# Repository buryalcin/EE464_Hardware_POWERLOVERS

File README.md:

# EE464_Hardware_POWERLOVERS
EE464 Hardware Project Repo by Burak Yalçın &amp; Emre Deniz Şenel

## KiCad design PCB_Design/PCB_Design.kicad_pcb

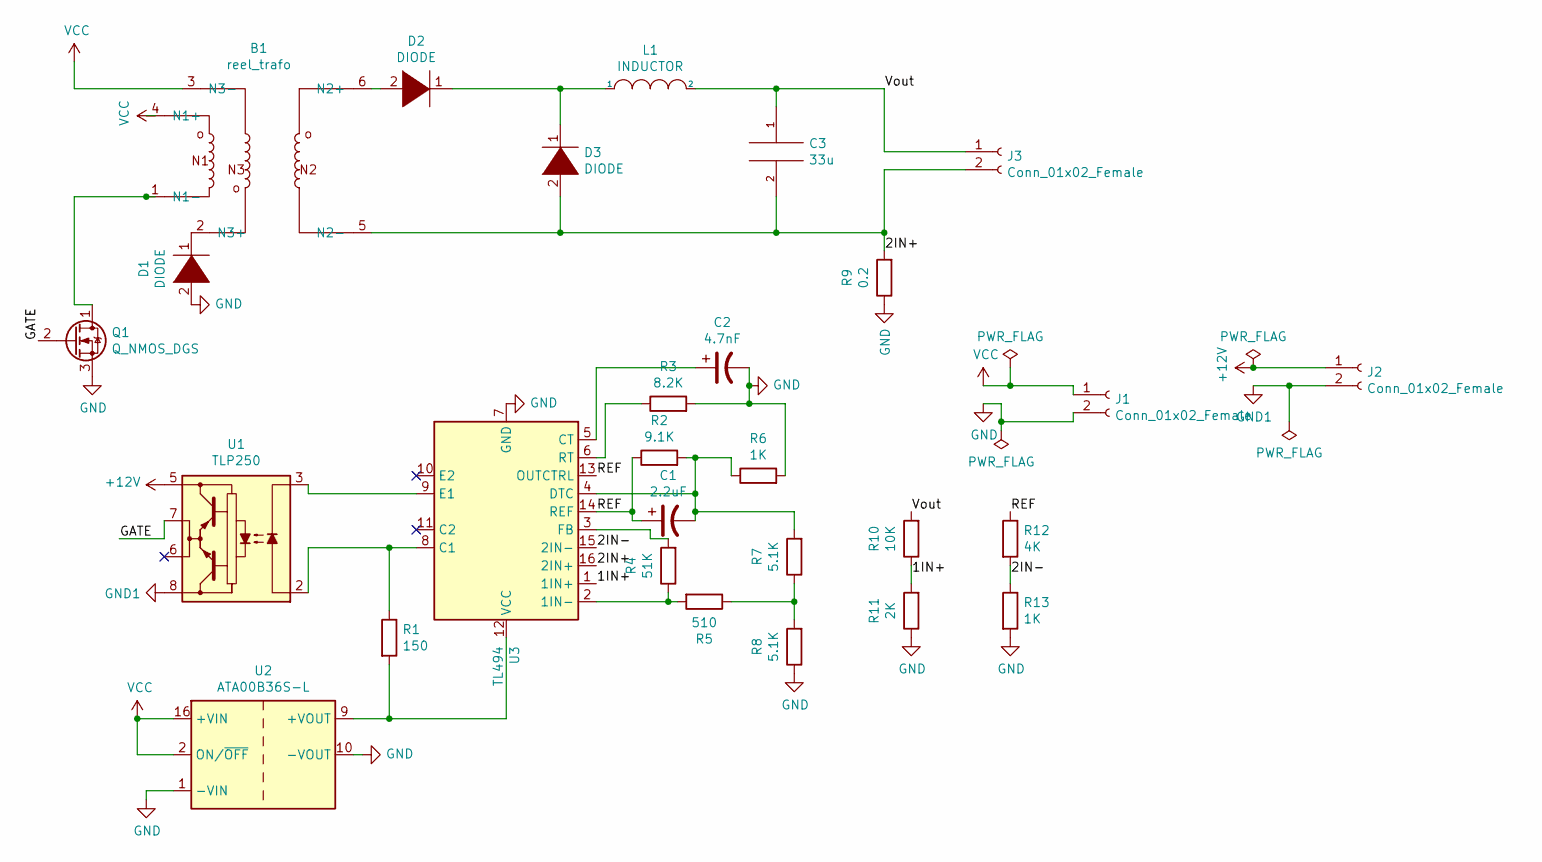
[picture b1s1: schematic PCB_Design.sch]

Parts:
B1: reel_trafo; trafo
C1: 2.2uF; C_1206_3216Metric_Pad1.42x1.75mm_HandSolder
C2: 4.7nF; C_1206_3216Metric_Pad1.42x1.75mm_HandSolder
C3: 33u; C_1206_3216Metric_Pad1.42x1.75mm_HandSolder
D1, D2, D3: DIODE; TO-277A
J1, J2, J3: Conn_01x02_Female; Banana_Jack_2Pin
L1: INDUCTOR; L_Toroid_Horizontal_D32.5mm_P28.90mm_Bourns_2300
Q1: Q_NMOS_DGS; PQFN_8x8
R1: 150; R_Axial_DIN0309_L9.0mm_D3.2mm_P12.70mm_Horizontal
R2: 9.1K; R_Axial_DIN0309_L9.0mm_D3.2mm_P12.70mm_Horizontal
R3: 8.2K; R_Axial_DIN0309_L9.0mm_D3.2mm_P12.70mm_Horizontal
R4: 51K; R_Axial_DIN0309_L9.0mm_D3.2mm_P12.70mm_Horizontal
R5: 510; R_Axial_DIN0309_L9.0mm_D3.2mm_P12.70mm_Horizontal
R6, R13: 1K; R_Axial_DIN0309_L9.0mm_D3.2mm_P12.70mm_Horizontal
R7, R8: 5.1K; R_Axial_DIN0309_L9.0mm_D3.2mm_P12.70mm_Horizontal
R9: 0.2; R_Axial_DIN0309_L9.0mm_D3.2mm_P12.70mm_Horizontal
R10: 10K; R_Axial_DIN0309_L9.0mm_D3.2mm_P12.70mm_Horizontal
R11: 2K; R_Axial_DIN0309_L9.0mm_D3.2mm_P12.70mm_Horizontal
R12: 4K; R_Axial_DIN0309_L9.0mm_D3.2mm_P12.70mm_Horizontal
U1: TLP250; DIP-8_W7.62mm
U2: ATA00B36S-L; Converter_DCDC_Artesyn_ATA_SMD
U3: TL494; DIP-16_W7.62mm

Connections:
+12V: J2.1, U1.5 (VEE)
/1IN+: R10.1, R11.2, U3.1 (1IN+)
/2IN+: B1.5 (N2-), C3.2, D3.2 (K), J3.2, R9.2, U3.16 (2IN+)
/2IN-: R12.2, R13.1, U3.15 (2IN-)
/GATE: Q1.2 (G), U1.7 (VO)
/REF: C1.1, R2.1, R12.1, U3.13 (OUTCTRL), U3.14 (REF)
/Vout: C3.1, J3.1, L1.2, R10.2
GND: C2.2, D1.2 (K), J1.2, Q1.3 (S), R3.2, R6.2, R8.1, R9.1, R11.1, R13.2, U2.1 (-VIN), U2.10 (-VOUT), U3.7 (GND)
GND1: J2.2, U1.8 (VCC)
unnamed: B1.1 (N1-), Q1.1 (D)
unnamed: B1.2 (N3+), D1.1 (A)
unnamed: B1.6 (N2+), D2.2 (K)
unnamed: C1.2, R2.2, R6.1, R7.2, U3.4 (DTC)
unnamed: C2.1, U3.5 (CT)
unnamed: D2.1 (A), D3.1 (A), L1.1
unnamed: R1.1, U1.2 (A), U3.8 (C1)
unnamed: R1.2, U2.9 (+VOUT), U3.12 (VCC)
unnamed: R3.1, U3.6 (RT)
unnamed: R4.1, R5.2, U3.2 (1IN-)
unnamed: R4.2, U3.3 (FB)
unnamed: R5.1, R7.1, R8.2
unnamed: U1.3 (C), U3.9 (E1)
VCC: B1.3 (N3-), B1.4 (N1+), J1.1, U2.2 (ON/~OFF), U2.16 (+VIN)

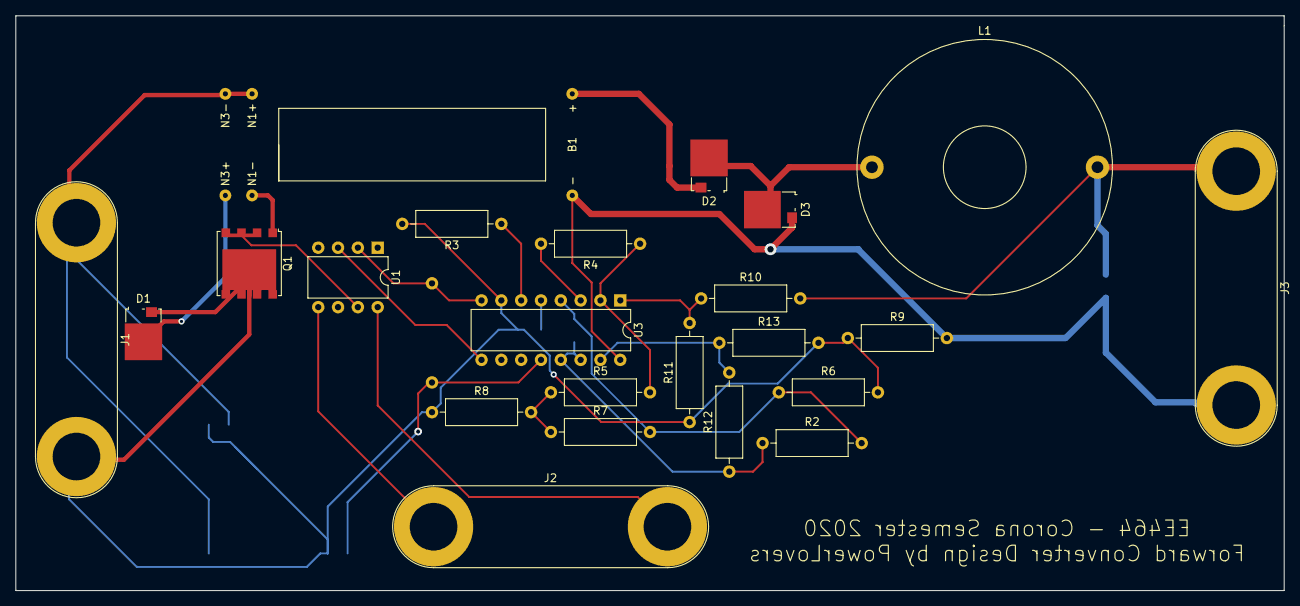
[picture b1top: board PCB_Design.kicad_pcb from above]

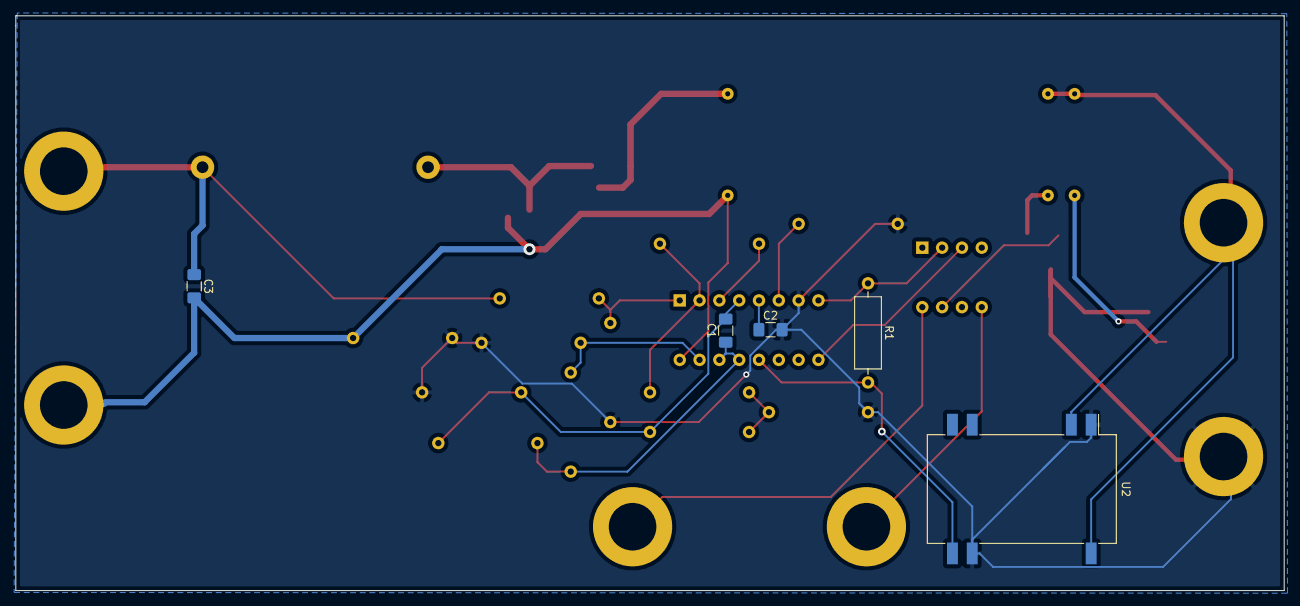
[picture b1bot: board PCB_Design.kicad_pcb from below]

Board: 2 copper layers, 162.6 x 73.7 mm, 28 parts (5 on the bottom side), 23 nets.

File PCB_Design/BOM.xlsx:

Reference | Quantity | Value | Footprint | Price | Total Price | Datasheet
B1 | 1 | trafo | Transformer_THT:trafo | 4 | 4 | https://www.mag-inc.com/Media/Magnetics/Datasheets/0F43515EC.pdf
C1 | 1 | 2.2uF | Capacitor_SMD:C_1206_3216Metric_Pad1.42x1.75mm_HandSolder | 0.28999999999999998 | 0.28999999999999998 | https://www.digikey.com/product-detail/en/murata-electronics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
C2 | 1 | 4.7nF | Capacitor_SMD:C_1206_3216Metric_Pad1.42x1.75mm_HandSolder | 0.1 | 0.1 | https://www.digikey.com/product-detail/en/murata-electronics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
C3 | 1 | 33u | Capacitor_SMD:C_1206_3216Metric_Pad1.42x1.75mm_HandSolder | 1.2 | 1.2 | https://product.tdk.com/info/en/documents/chara_sheet/C3216J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
D1 D2 D3 | 3 | DIODE | Package_TO_SOT_SMD:TO-277A | 0.62 | 1.8599999999999999 | https://www.digikey.com/product-detail/en/vishay-semiconduct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
J1 J2 J3 | 3 | Conn_01x02_Female | Connector:Banana_Jack_2Pin | 1.44 | 4.32 | https://www.digikey.com/product-detail/en/cinch-connectivity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
L1 | 1 | INDUCTOR | Inductor_THT:L_Toroid_Horizontal_D32.5mm_P28.90mm_Bourns_2300 | 2.83 | 2.83 | https://www.digikey.com/product-detail/en/bourns-inc/2300LL-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
Q1 | 1 | Q_NMOS_DGS | Package_TO_SOT_SMD:PQFN_8x8 | 1.82 | 1.82 | https://www.digikey.com/product-detail/en/on-semiconductor/F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
R1 | 1 | 150 | Resistor_THT:R_Axial_DIN0309_L9.0mm_D3.2mm_P12.70mm_Horizontal | 0.1 | 0.1 | https://www.digikey.com/product-detail/en/stackpole-electron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
R10 | 1 | 10K | Resistor_THT:R_Axial_DIN0309_L9.0mm_D3.2mm_P12.70mm_Horizontal | 0.1 | 0.1 | https://www.digikey.com/product-detail/en/stackpole-electron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
R11 | 1 | 2K | Resistor_THT:R_Axial_DIN0309_L9.0mm_D3.2mm_P12.70mm_Horizontal | 0.1 | 0.1 | https://www.digikey.com/product-detail/en/stackpole-electron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
R12 | 1 | 4K | Resistor_THT:R_Axial_DIN0309_L9.0mm_D3.2mm_P12.70mm_Horizontal | 0.63 | 0.63 | https://www.digikey.com/product-detail/en/vishay-dale/CMF554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
R2 | 1 | 9.1K | Resistor_THT:R_Axial_DIN0309_L9.0mm_D3.2mm_P12.70mm_Horizontal | 0.63 | 0.63 | https://www.digikey.com/product-detail/en/yageo/MFP-25BRD52-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
R3 | 1 | 8.2K | Resistor_THT:R_Axial_DIN0309_L9.0mm_D3.2mm_P12.70mm_Horizontal | 0.1 | 0.1 | https://www.digikey.com/product-detail/en/stackpole-electron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
R4 | 1 | 51K | Resistor_THT:R_Axial_DIN0309_L9.0mm_D3.2mm_P12.70mm_Horizontal | 0.1 | 0.1 | https://www.digikey.com/product-detail/en/stackpole-electron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
R5 | 1 | 510 | Resistor_THT:R_Axial_DIN0309_L9.0mm_D3.2mm_P12.70mm_Horizontal | 0.1 | 0.1 | https://www.digikey.com/product-detail/en/stackpole-electron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
R6 R13 | 2 | 1K | Resistor_THT:R_Axial_DIN0309_L9.0mm_D3.2mm_P12.70mm_Horizontal | 0.1 | 0.2 | https://www.digikey.com/product-detail/en/stackpole-electron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
R7 R8 | 2 | 5.1K | Resistor_THT:R_Axial_DIN0309_L9.0mm_D3.2mm_P12.70mm_Horizontal | 0.1 | 0.2 | https://www.digikey.com/product-detail/en/stackpole-electron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
R9 | 1 | 0.2 | Resistor_THT:R_Axial_DIN0309_L9.0mm_D3.2mm_P12.70mm_Horizontal | 3.08 | 3.08 | https://www.digikey.com/product-detail/en/ohmite/15FR200E/15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
U1 | 1 | TLP250 | Package_DIP:DIP-8_W7.62mm | 1.1499999999999999 | 1.1499999999999999 | http://toshiba.semicon-storage.com/info/docget.jsp?did=16821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
U2 | 1 | ATA00B36S-L | Converter_DCDC:Converter_DCDC_Artesyn_ATA_SMD | 16.39 | 16.39 | https://www.artesyn.com/power/assets/ata_series_ds_01apr2015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
U3 | 1 | TL494 | Package_DIP:DIP-16_W7.62mm | 0.53 | 0.53 | http://www.ti.com/lit/ds/symlink/tl494.pdf
 |  |  |  | Total Price : | 39.830000000000005
 |  |  | https://www.pcbway.com/QuickOrderOnline.aspx
 |  | Core Eq | https://www.digikey.com/product-detail/en/tdk-electronics-in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
 |  |  | Around 2 dollars
 |  | Cable | AWG #22 - Around 2 dollars

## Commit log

2020-06-15 Transformator and inductor calculations have been done again with commercial products. We recently worked on the available products, cores, cables etc. However, due to pandemic, now in the software v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
2020-06-15 pcb design schematic part is near completion
2020-06-16 schematic and footprint assoc are done
2020-06-17 started layout
2020-06-19 started pcb design, looking good for a newbie
2020-06-19 pcb design completed
2020-06-21 Report is started, most of the parts are done. Compansator design is done. LTSpice model is done. All the files are added, ideal and non-ideal models included.
2020-06-23 design completed. gerber files and bom are added
2020-06-24 The report is finished. All calculations are in the excel file and matlab files. We added bom pdf and other pdfs as well. Project is finished!
